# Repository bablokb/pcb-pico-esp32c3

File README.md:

Pico - ESP32C3 Super-Mini Connector
===================================

In this repository you will find the KiCAD (v7) design-files for a small PCB
that connects the Pico UART-pins GP0/GP1 with the ESP32C3-SuperMini UART1-pins.

If the ESP32C3 is flashed with the [AT-firmware](https://github.com/espressif/esp-at),
the Pico can communicate directly with the C3.

See <https://github.com/bablokb/circuitpython-esp32at> for a software solution.

Ready to use production files for JLCPCB are in the directory `production_files/`.

Schematic
---------

Layout
------

3D-Views
--------

License
-------

[![CC BY-SA 4.0][cc-by-sa-shield]][cc-by-sa]

This work is licensed under a
[Creative Commons Attribution-ShareAlike 4.0 International
License][cc-by-sa].

[![CC BY-SA 4.0][cc-by-sa-image]][cc-by-sa]

[cc-by-sa]: http://creativecommons.org/licenses/by-sa/4.0/
[cc-by-sa-image]: https://licensebuttons.net/l/by-sa/4.0/88x31.png
[cc-by-sa-shield]:
https://img.shields.io/badge/License-CC%20BY--SA%204.0-lightgrey.svg

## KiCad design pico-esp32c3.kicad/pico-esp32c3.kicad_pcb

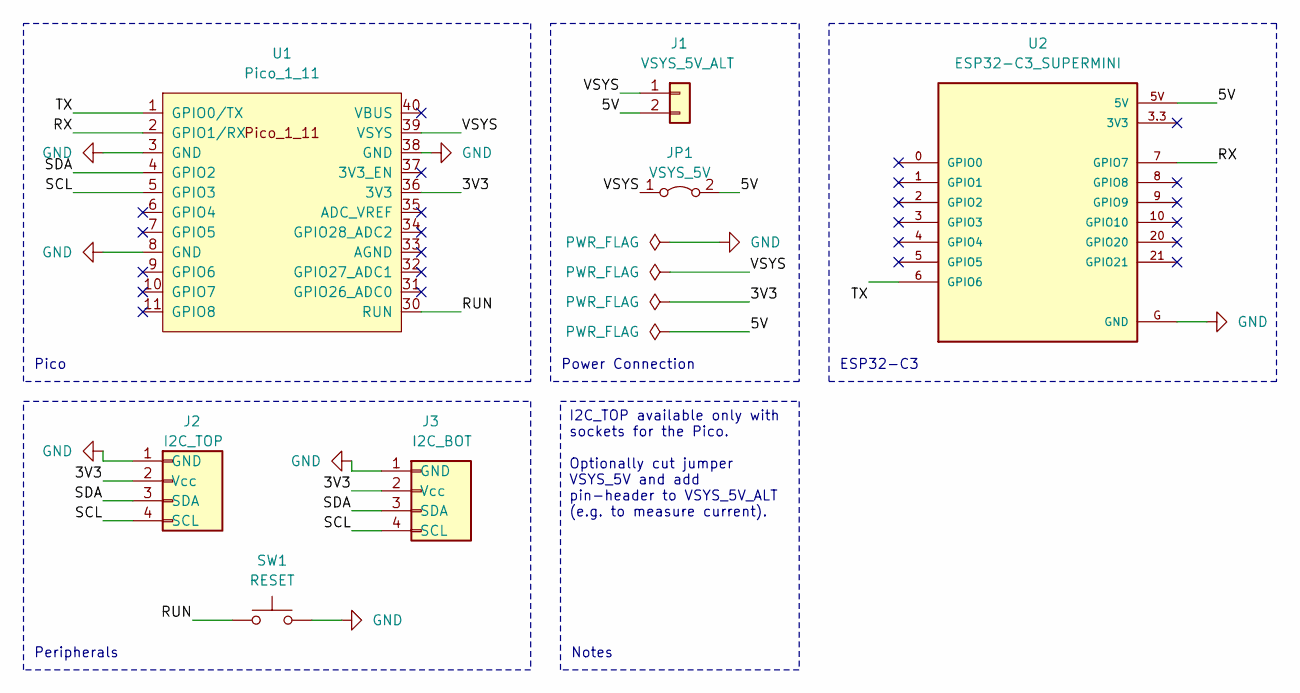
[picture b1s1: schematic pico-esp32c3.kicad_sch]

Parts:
J1: VSYS_5V_ALT; PinHeader_1x02_P2.54mm_Vertical
J2: I2C_TOP; JST_SH_SM04B-SRSS-TB_1x04-1MP_P1.00mm_Horizontal
J3: I2C_BOT; JST_SH_SM04B-SRSS-TB_1x04-1MP_P1.00mm_Horizontal
JP1: VSYS_5V; SolderJumper-2_P1.3mm_Bridged_Pad1.0x1.5mm
SW1: RESET; SW_PUSH_SLIM_1x4
U1: Pico_1_11; RPi_Pico_SMD_TH_1_11
U2: ESP32-C3_SUPERMINI

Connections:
/3V3: J2.2 (Vcc), J3.2 (Vcc), U1.36 (3V3)
/5V: J1.2, JP1.2 (B), U2.5V
/RUN: SW1.1, U1.30 (RUN)
/RX: U1.2 (GPIO1/RX), U2.7 (GPIO7)
/SCL: J2.4 (SCL), J3.4 (SCL), U1.5 (GPIO3)
/SDA: J2.3 (SDA), J3.3 (SDA), U1.4 (GPIO2)
/TX: U1.1 (GPIO0/TX), U2.6 (GPIO6)
/VSYS: J1.1, JP1.1 (A), U1.39 (VSYS)
GND: J2.1 (GND), J3.1 (GND), SW1.2, U1.3 (GND), U1.8 (GND), U1.38 (GND), U2.G (GND)

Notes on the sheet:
I2C_TOP available only with sockets for the Pico. Optionally cut jumper VSYS_5V and add pin-header to VSYS_5V_ALT (e.g. to measure current).
Power Connection
Notes
Pico
ESP32-C3
Peripherals

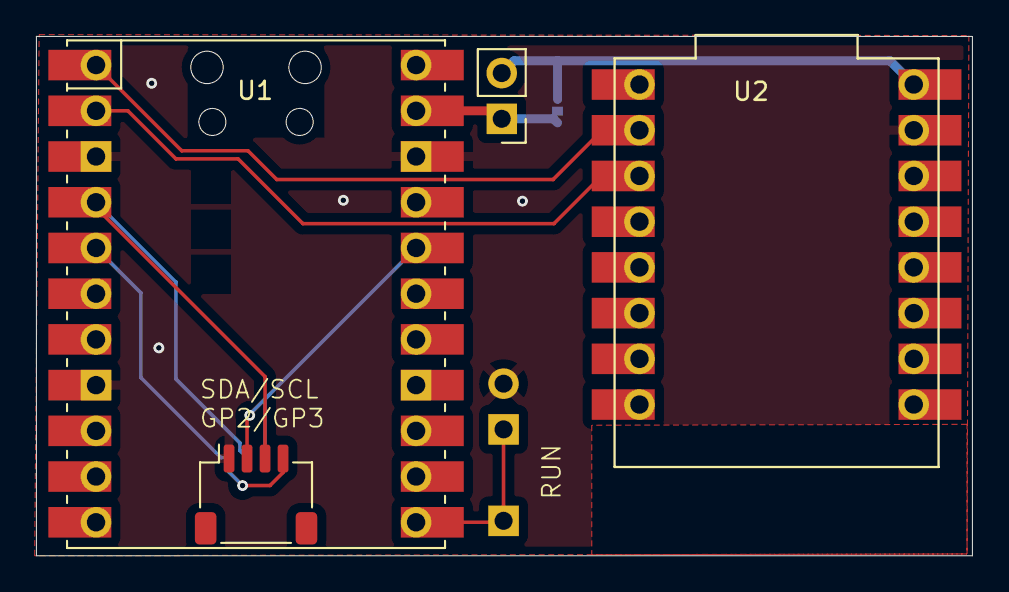
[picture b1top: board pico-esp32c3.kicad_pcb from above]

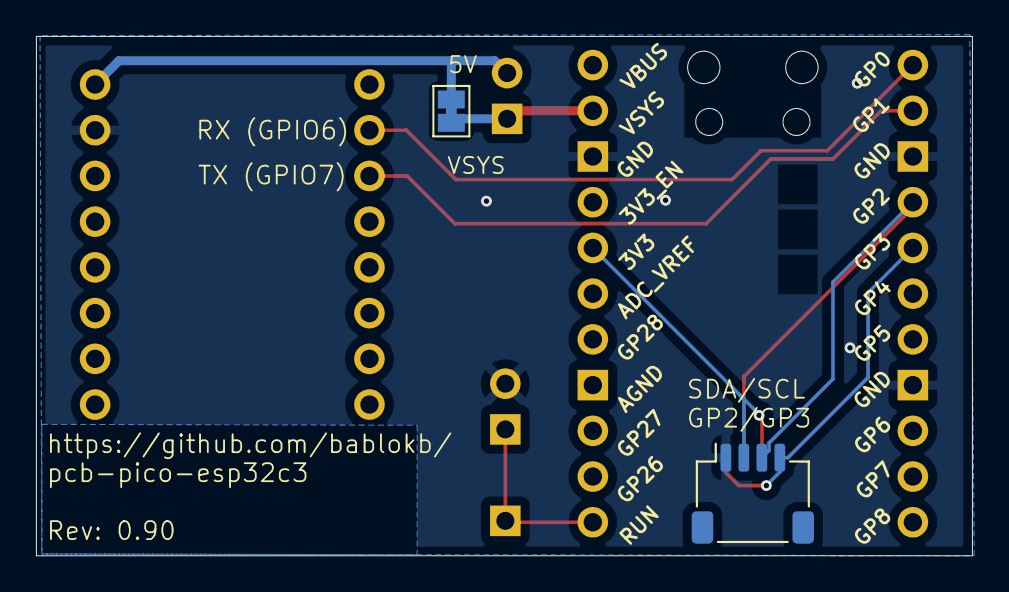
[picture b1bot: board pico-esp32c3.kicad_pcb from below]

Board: 2 copper layers, 52.0 x 28.9 mm, 7 parts (2 on the bottom side), 9 nets.

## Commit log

2024-09-23 initial commit to the repo
2024-09-23 added content
